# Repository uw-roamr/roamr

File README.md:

# ROAMR: Really Opensource Autonomous Mobile Robot

Mobile phones and mobile robots have many common requirements:

- performant sensors (cameras, IMUs, LiDAR, GPS) and sensor fusion
- networking capabilities (WiFi, Bluetooth Low Energy, LTE)
- energy efficiency

What if we turned the iPhone into a robot?

## Architecture

### iOS host app:

- exposes the core sensor data through iOS APIs
    - Camera
    - LiDAR (iPhone Pro 12+)
    - IMU
- runs WASM bytecode using statically compiled WAMR iwasm
- communicates with ESP32 over BLE to control motors

### WASM module:

- imports read sensor functions from iOS host
- multi-threaded application with autonomy logic
- compiled using WASI-SDK and threading
    - C++: https://github.com/WebAssembly/wasi-sdk

### ESP32:

- recieves commands over BLE and uses SimpleFOC to control motors

## Setup

```sh
pip install pre-commit
pre-commit
```

## Run App with Robot
- Open/build iOS app.
- Connect to bluetooth using the app
- Drive robot!

### Optional:
- Open HTML page in webpage folder.
- Run websocket on the websocket page of the app
- Connect to app websocket
- Drive robot!

## Development

See [WASM/README.md](WASM/README.md)

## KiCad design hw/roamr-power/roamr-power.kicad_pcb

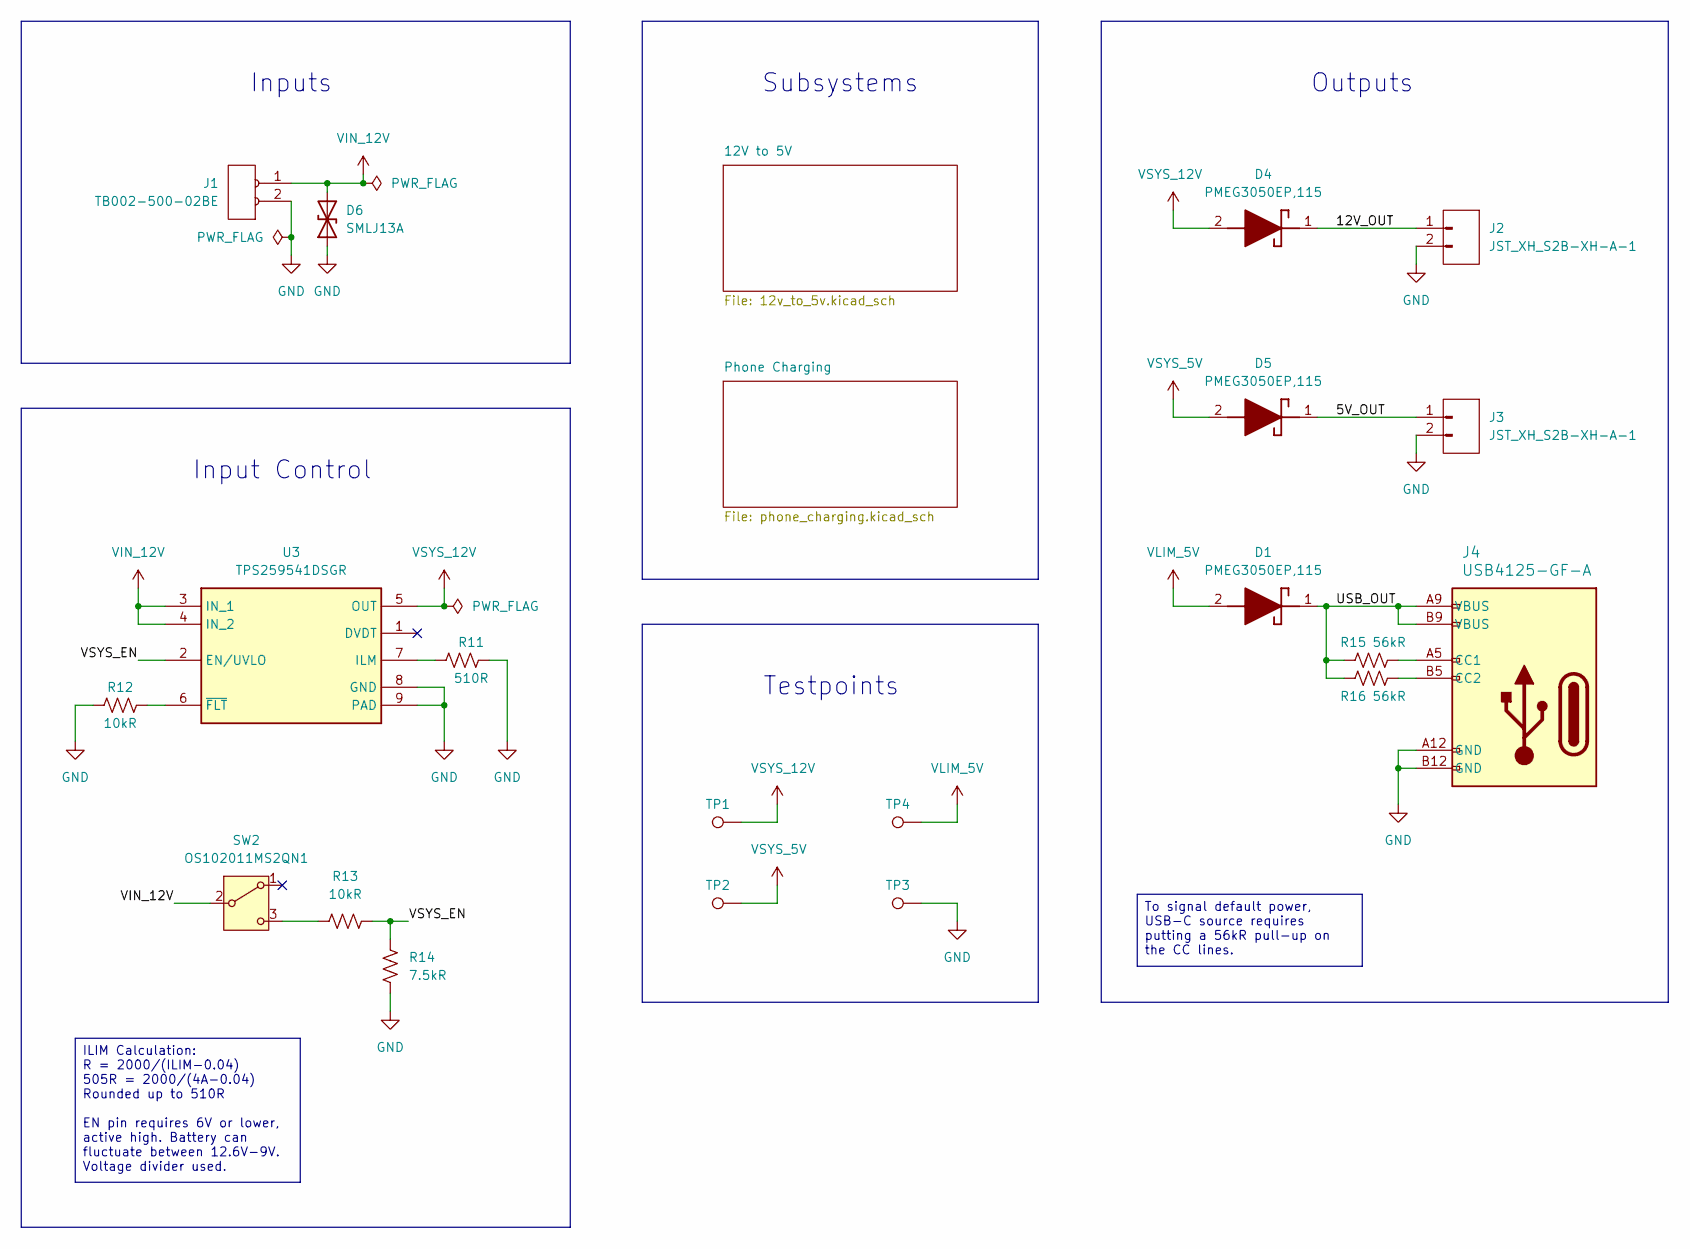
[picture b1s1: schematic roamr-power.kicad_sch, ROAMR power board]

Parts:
D1, D4, D5: PMEG3050EP,115; PMEG3050EP115; Mouser Part Number 771-PMEG3050EP115
D6: SMLJ13A; DIOM7959X262N; Manufacturer_Part_Number SMLJ13A
J1: TB002-500-02BE; TB00250002BE; Manufacturer_Part_Number TB002-500-02BE
J2, J3: JST_XH_S2B-XH-A-1; JST_XH_S2B-XH-A-1_1x02_P2.50mm_Horizontal; Manufacturer_Part_Number JST_XH_S2B-XH-A-1
J4: USB4125-GF-A; USB4125GFA; Manufacturer_Part_Number USB4125-GF-A
R11: 510R; R_0603_1608Metric
R12, R13: 10kR; R_0603_1608Metric
R14: 7.5kR; R_0603_1608Metric
R15, R16: 56kR; R_0603_1608Metric
SW2: OS102011MS2QN1; OS102011MA1QN1; Manufacturer_Part_Number OS102011MS2QN1
TP1, TP2, TP4: TestPoint; TestPoint_Pad_D1.5mm
TP3: TestPoint; TestPoint_Keystone_5005-5009_Compact; Manufacturer_Part_Number 5005-5009
U3: TPS259541DSGR; SON50P200X200X80-9N; Mouser Part Number 595-TPS259541DSGR

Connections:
/5V_OUT: D5.1 (K), J3.1
/12V_OUT: D4.1 (K), J2.1
/USB_OUT: D1.1 (K), J4.A9 (VBUS), J4.B4 (VBUS), J4.B9 (VBUS), R15.1, R16.1
/VSYS_EN: R13.2, R14.1, U3.2 (EN/UVLO)
GND: D6.1 (A1), J1.2, J2.2, J3.2, J4.A12 (GND), J4.B12 (GND), R11.2, R12.1, R14.2, TP3.1, U3.8 (GND), U3.9 (PAD); also elsewhere on the board
unnamed: J4.A5 (CC1), R15.2
unnamed: J4.B5 (CC2), R16.2
unnamed: R13.1, SW2.3 (C)
unnamed: R11.1, U3.7 (ILM)
unnamed: R12.2, U3.6 (~FLT)
VIN_12V: D6.2 (A2), J1.1, SW2.2 (B), U3.3 (IN_1), U3.4 (IN_2)
VLIM_5V: D1.2 (A), TP4.1; also elsewhere on the board
VSYS_5V: D5.2 (A), TP2.1; also elsewhere on the board
VSYS_12V: D4.2 (A), TP1.1, U3.5 (OUT); also elsewhere on the board

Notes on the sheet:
Input Control
Inputs
Subsystems
Outputs
Testpoints
ILIM Calculation: R = 2000/(ILIM-0.04) 505R = 2000/(4A-0.04) Rounded up to 510R EN pin requires 6V or lower, active high. Battery can fluctuate between 12.6V-9V. Voltage divider used.
To signal default power, USB-C source requires putting a 56kR pull-up on the CC lines.

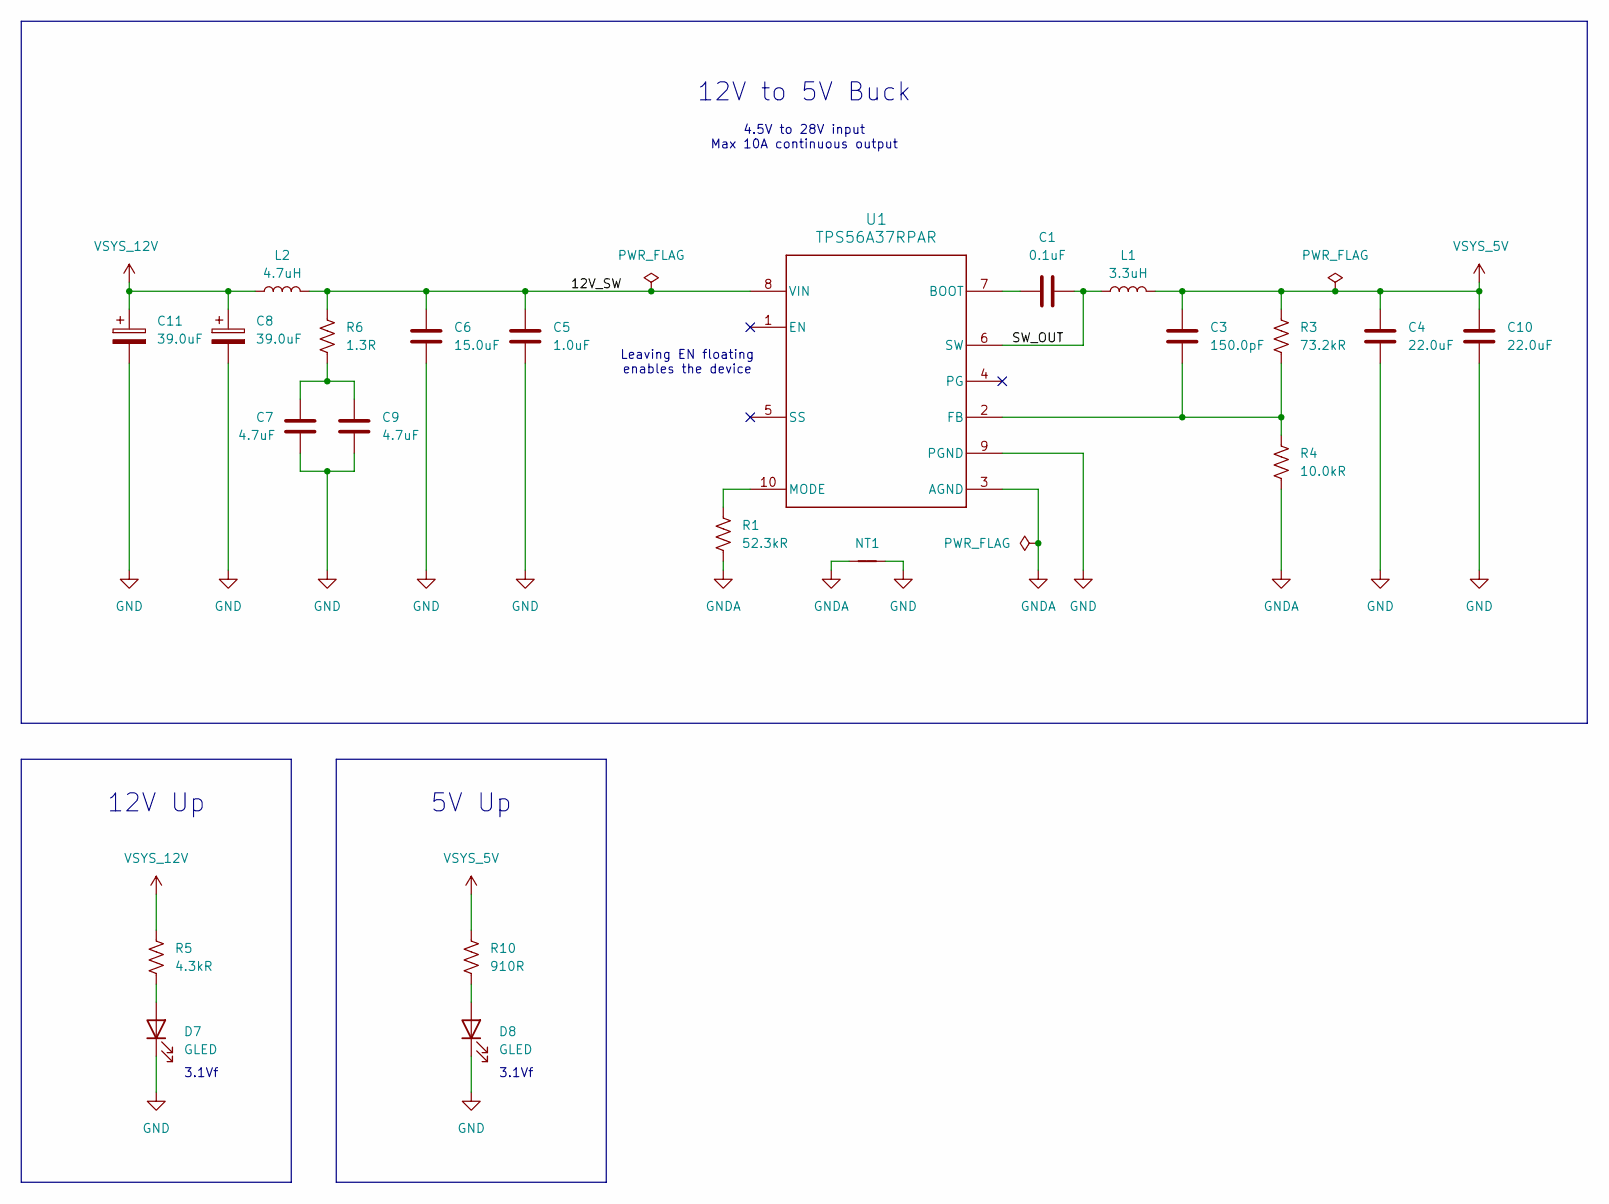
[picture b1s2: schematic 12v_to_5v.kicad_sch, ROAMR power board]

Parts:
C1: 0.1uF; C_0603_1608Metric
C3: 150.0pF; C_0603_1608Metric
C4, C10: 22.0uF; C_0603_1608Metric
C5: 1.0uF; C_0603_1608Metric
C6: 15.0uF; C_0805_2012Metric
C7, C9: 4.7uF; C_0603_1608Metric
C8, C11: 39.0uF; 16SVF270M
D7, D8: GLED; LEDC1608X70N; Manufacturer_Part_Number KT-0603G
L1: 3.3uH; IND_PCC-M0645M_PAN-L; Manufacturer_Part_Number ETQ-L4M3R3YFN
L2: 4.7uH; IND_VLS6045EX-4R7M_TDK; Manufacturer_Part_Number VLS6045EX
NT1: NetTie_2; NetTie-2_SMD_Pad0.5mm
R1: 52.3kR; R_0603_1608Metric
R3: 73.2kR; R_0603_1608Metric
R4: 10.0kR; R_0603_1608Metric
R5: 4.3kR; R_0603_1608Metric
R6: 1.3R; R_0603_1608Metric
R10: 910R; R_0603_1608Metric
U1: TPS56A37RPAR; RPA0010A-MFG; Manufacturer_Part_Number TPS56A37RPAR

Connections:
/12V to 5V/12V_SW: C5.1, C6.1, L2.2, R6.1, U1.8 (VIN)
/12V to 5V/SW_OUT: C1.2, L1.1, U1.6 (SW)
GND: C4.2, C5.2, C6.2, C7.2, C8.2, C9.2, C10.2, C11.2, D7.1 (K), D8.1 (K), NT1.2, U1.9 (PGND); also elsewhere on the board
GNDA: NT1.1, R1.1, R4.1, U1.3 (AGND)
unnamed: C7.1, C9.1, R6.2
unnamed: D7.2 (A), R5.2
unnamed: D8.2 (A), R10.2
unnamed: C1.1, U1.7 (BOOT)
unnamed: C3.2, R3.1, R4.2, U1.2 (FB)
unnamed: R1.2, U1.10 (MODE)
VSYS_5V: C3.1, C4.1, C10.1, L1.2, R3.2, R10.1; also elsewhere on the board
VSYS_12V: C8.1, C11.1, L2.1, R5.1; also elsewhere on the board

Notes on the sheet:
5V Up
3.1Vf
12V to 5V Buck
12V Up
3.1Vf
Leaving EN floating enables the device
4.5V to 28V input Max 10A continuous output

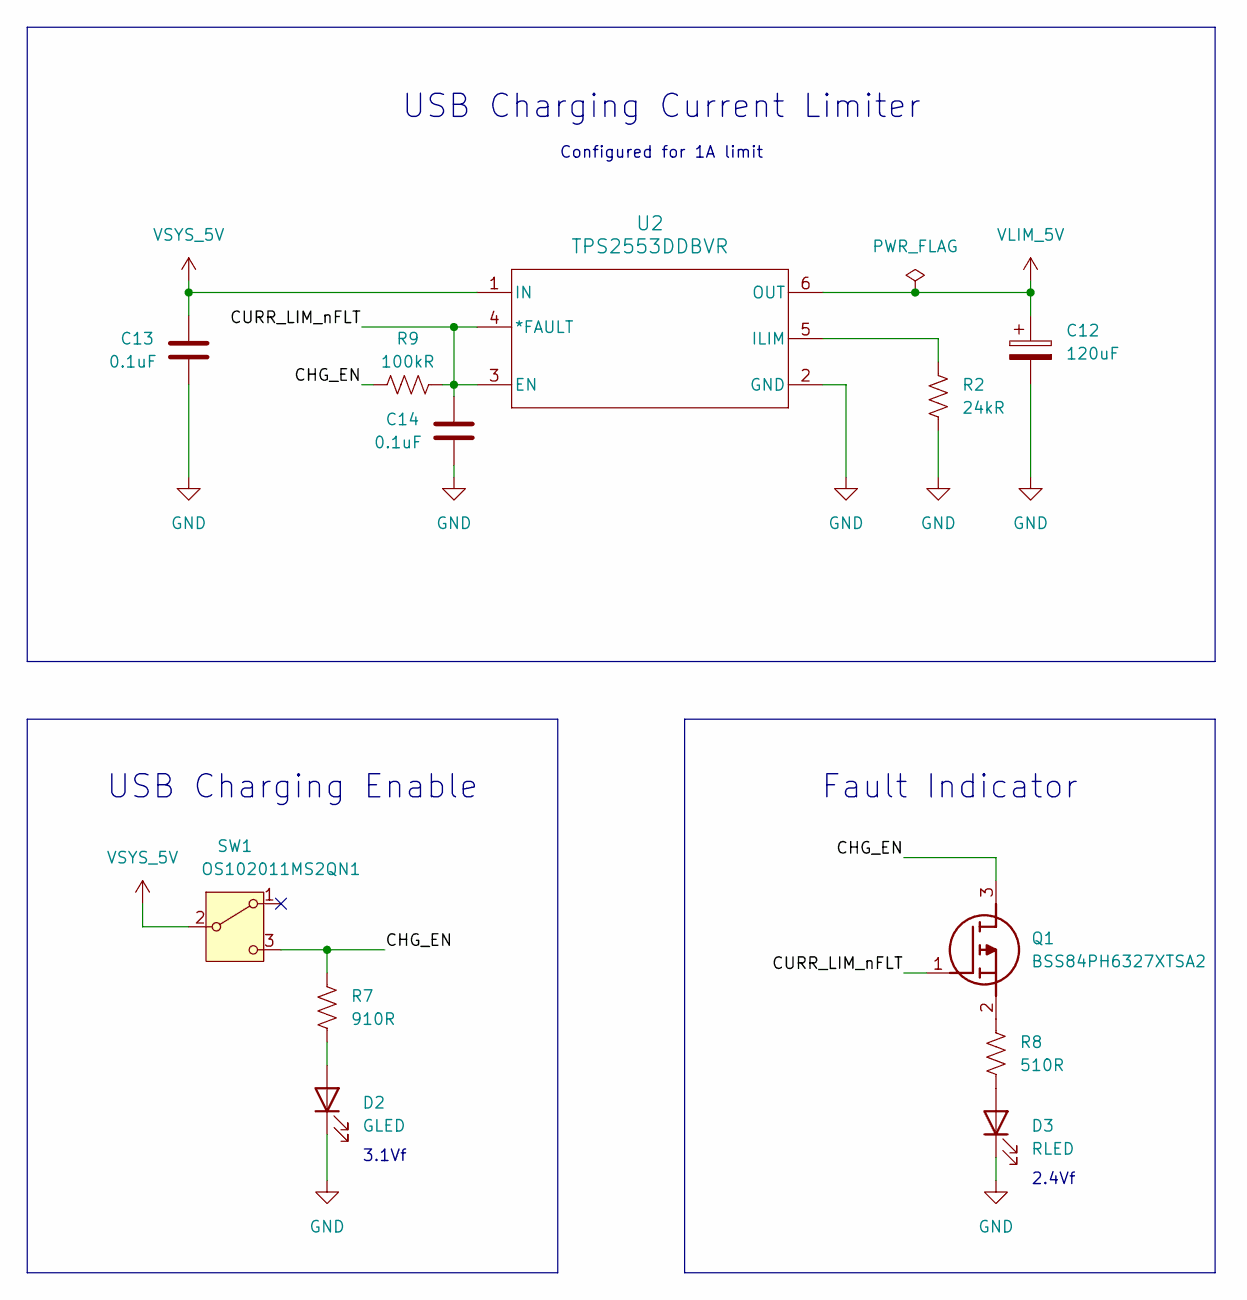
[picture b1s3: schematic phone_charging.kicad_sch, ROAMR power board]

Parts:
C12: 120uF; CAPAE660X610N
C13, C14: 0.1uF; C_0603_1608Metric
D2: GLED; LEDC1608X70N; Manufacturer_Part_Number KT-0603G
D3: RLED; LEDC1608X70N; Manufacturer_Part_Number KT-0603R
Q1: BSS84PH6327XTSA2; SOT95P240X110-3N; Mouser Part Number 726-BSS84PH6327XTSA2
R2: 24kR; R_0603_1608Metric
R7: 910R; R_0603_1608Metric
R8: 510R; R_0603_1608Metric
R9: 100kR; R_0603_1608Metric
SW1: OS102011MS2QN1; OS102011MA1QN1; Manufacturer_Part_Number OS102011MS2QN1
U2: TPS2553DDBVR; SOT95P280X145-6N; Manufacturer_Part_Number TPS2553DDBVR

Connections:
/Phone Charging/CHG_EN: Q1.3 (D), R7.1, R9.1, SW1.3 (C)
/Phone Charging/CURR_LIM_nFLT: C14.1, Q1.1 (G), R9.2, U2.3 (EN), U2.4 (*FAULT)
GND: C12.2, C13.2, C14.2, D2.1 (K), D3.1 (K), R2.2, U2.2 (GND); also elsewhere on the board
unnamed: D2.2 (A), R7.2
unnamed: D3.2 (A), R8.2
unnamed: Q1.2 (S), R8.1
unnamed: R2.1, U2.5 (ILIM)
VLIM_5V: C12.1, U2.6 (OUT); also elsewhere on the board
VSYS_5V: C13.1, SW1.2 (B), U2.1 (IN); also elsewhere on the board

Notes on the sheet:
USB Charging Enable
3.1Vf
USB Charging Current Limiter
2.4Vf
Fault Indicator
Configured for 1A limit

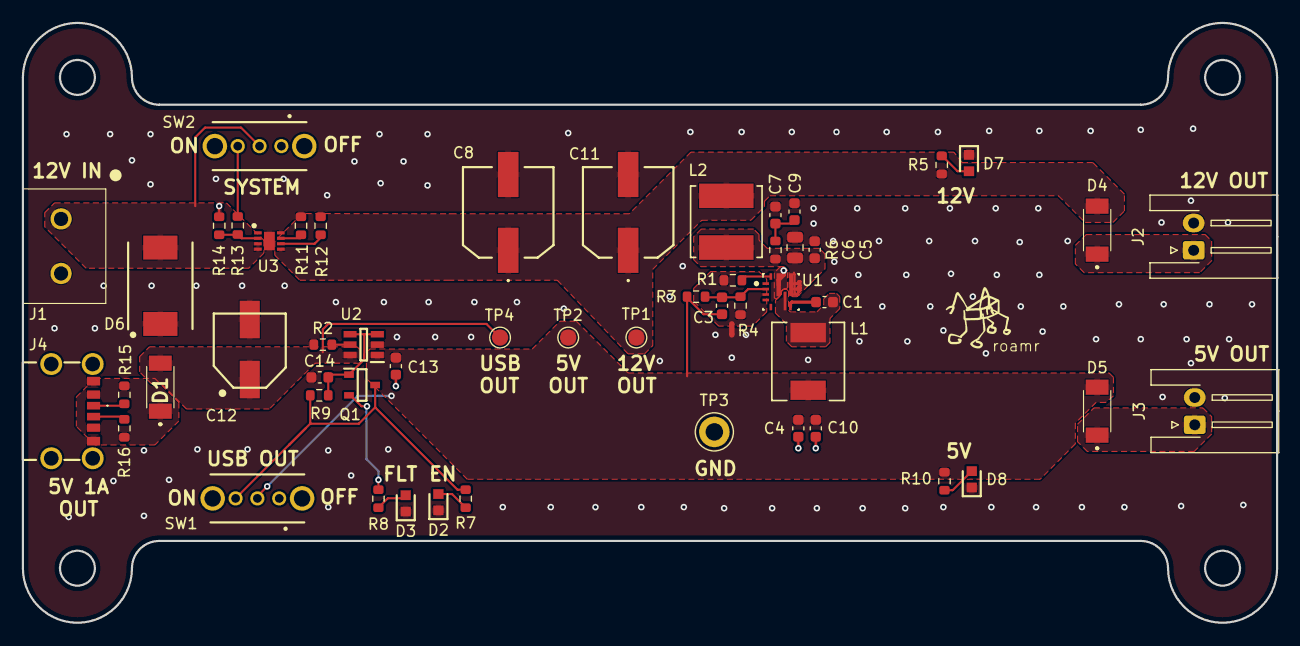
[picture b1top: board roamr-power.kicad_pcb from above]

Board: 2 copper layers, 115.0 x 55.0 mm, 54 parts (0 on the bottom side), 29 nets.

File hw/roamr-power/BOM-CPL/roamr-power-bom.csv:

"Reference","Qty","Value","Manufacturer_Part_Number","DNP","Exclude from BOM","Exclude from Board","Footprint","Datasheet"
"C1,C13,C14","3","0.1uF","","","","","Capacitor_SMD:C_0603_1608Metric","~"
"C3","1","150.0pF","","","","","Capacitor_SMD:C_0603_1608Metric","~"
"C4,C10","2","22.0uF","","","","","Capacitor_SMD:C_0603_1608Metric","~"
"C5","1","1.0uF","","","","","Capacitor_SMD:C_0603_1608Metric","~"
"C6","1","15.0uF","","","","","Capacitor_SMD:C_0805_2012Metric","~"
"C7,C9","2","4.7uF","","","","","Capacitor_SMD:C_0603_1608Metric","~"
"C8,C11","2","39.0uF","","","","","35SVPF39M:16SVF270M","~"
"C12","1","120uF","","","","","GYG1E121MCQ1GS:CAPAE660X610N","~"
"D1,D4,D5","3","PMEG3050EP,115","PMEG3050EP,115","","","","PMEG3050EP:PMEG3050EP115","https://assets.nexperia.com/documents/data-sheet/PMEG3050EP.pdf"
"D2,D7,D8","3","GLED","KT-0603G","","","","KT-0603:LEDC1608X70N","~"
"D3","1","RLED","KT-0603R","","","","KT-0603:LEDC1608X70N","~"
"D6","1","SMLJ13A","SMLJ13A","","","","SMLJ13CA-R:DIOM7959X262N","~"
"J1","1","TB002-500-02BE","TB002-500-02BE","","","","TB002-500-02BE:TB00250002BE","~"
"J2,J3","2","JST_XH_S2B-XH-A-1","JST_XH_S2B-XH-A-1","","","","Connector_JST:JST_XH_S2B-XH-A-1_1x02_P2.50mm_Horizontal","~"
"J4","1","USB4125-GF-A","USB4125-GF-A","","","","USB4125-GF-A:USB4125GFA","USB4125-GF-A"
"L1","1","3.3uH","ETQ-L4M3R3YFN","","","","ETQ-P4M3R3YFN:IND_PCC-M0645M_PAN-L","~"
"L2","1","4.7uH","VLS6045EX","","","","VLS6045EX_4R7M:IND_VLS6045EX-4R7M_TDK","~"
"NT1","1","NetTie_2","","","Excluded from BOM","","NetTie:NetTie-2_SMD_Pad0.5mm","~"
"Q1","1","BSS84PH6327XTSA2","BSS84PH6327XTSA2","","","","BSS84PH6327XTSA2:SOT95P240X110-3N","https://componentsearchengine.com/Datasheets/2/BSS84PH6327XTSA2.pdf"
"R1","1","52.3kR","","","","","Resistor_SMD:R_0603_1608Metric","~"
"R2","1","24kR","","","","","Resistor_SMD:R_0603_1608Metric","~"
"R3","1","73.2kR","","","","","Resistor_SMD:R_0603_1608Metric","~"
"R4","1","10.0kR","","","","","Resistor_SMD:R_0603_1608Metric","~"
"R5","1","4.3kR","","","","","Resistor_SMD:R_0603_1608Metric","~"
"R6","1","1.3R","","","","","Resistor_SMD:R_0603_1608Metric","~"
"R7,R10","2","910R","","","","","Resistor_SMD:R_0603_1608Metric","~"
"R8,R11","2","510R","","","","","Resistor_SMD:R_0603_1608Metric","~"
"R9","1","100kR","","","","","Resistor_SMD:R_0603_1608Metric","~"
"R12,R13","2","10kR","","","","","Resistor_SMD:R_0603_1608Metric","~"
"R14","1","7.5kR","","","","","Resistor_SMD:R_0603_1608Metric","~"
"R15,R16","2","56kR","","","","","Resistor_SMD:R_0603_1608Metric","~"
"SW1,SW2","2","OS102011MS2QN1","OS102011MS2QN1","","","","OS102011MS2QN1:OS102011MA1QN1","~"
"TP1,TP2,TP4","3","TestPoint","","","","","TestPoint:TestPoint_Pad_D1.5mm","~"
"TP3","1","TestPoint","5005-5009","","","","TestPoint:TestPoint_Keystone_5005-5009_Compact","~"
"U1","1","TPS56A37RPAR","TPS56A37RPAR","","","","TPS56A37RPAR:RPA0010A-MFG","https://www.ti.com/lit/gpn/tps56a37"
"U2","1","TPS2553DDBVR","TPS2553DDBVR","","","","TPS2553DDBVR:SOT95P280X145-6N","https://www.ti.com/lit/gpn/tps2553d"
"U3","1","TPS259541DSGR","TPS259541DSGR","","","","TPS259541DSGR:SON50P200X200X80-9N","http://www.ti.com/lit/gpn/tps2595"

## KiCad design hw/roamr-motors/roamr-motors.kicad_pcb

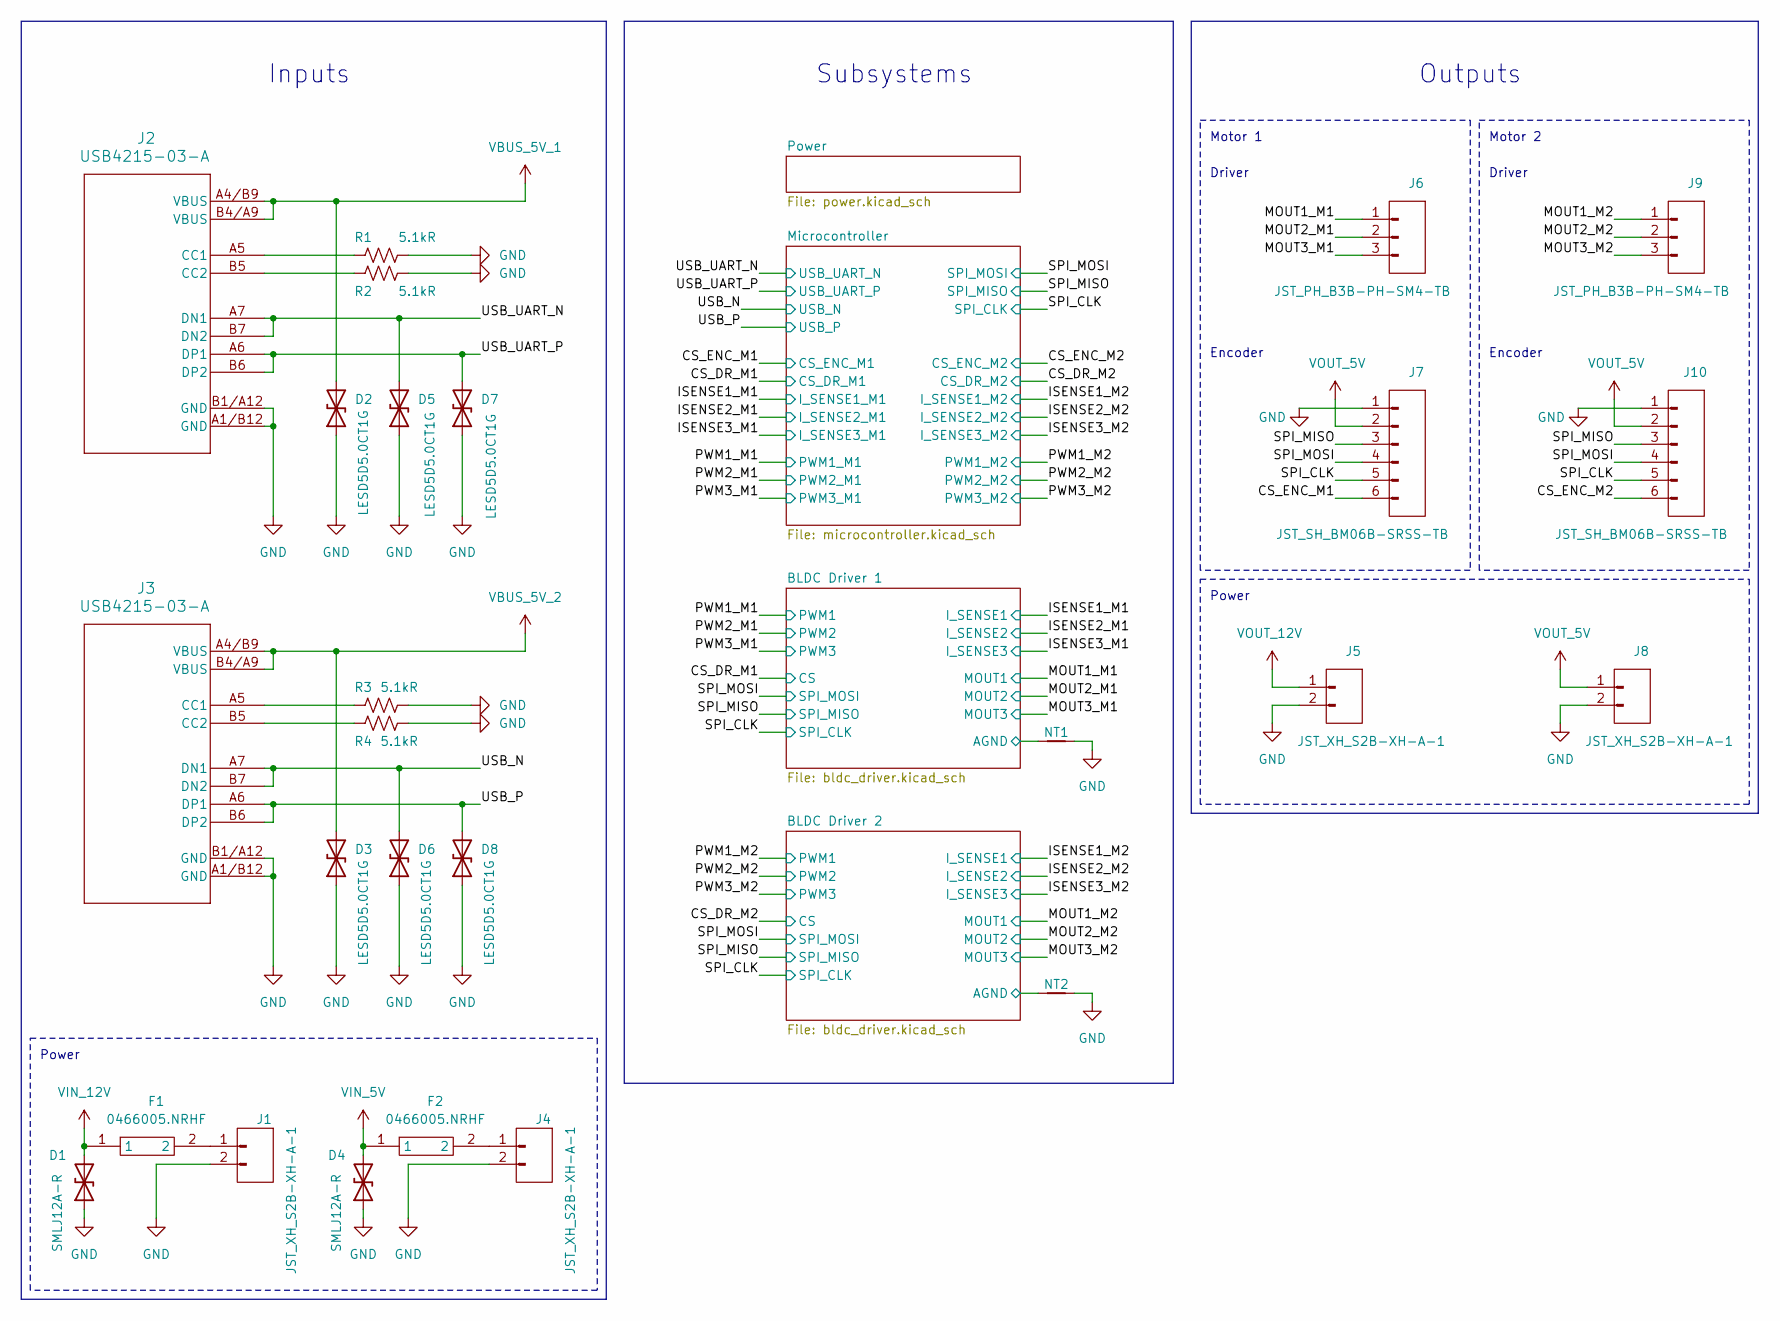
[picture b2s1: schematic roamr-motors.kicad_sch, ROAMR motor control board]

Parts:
D1, D4: SMLJ12A-R; DIOM7959X262N
D2, D3, D5, D6, D7, D8: LESD5D5.0CT1G; LESD5D50CT1G
F1, F2: 0466005.NRHF; F1206; LCSC Part C57525
J1, J4, J5, J8: JST_XH_S2B-XH-A-1; JST_XH_S2B-XH-A-1_1x02_P2.50mm_Horizontal
J2, J3: USB4215-03-A; CONN_8p94X6p5X3p16_12L_GCC
J6, J9: JST_PH_B3B-PH-SM4-TB; JST_PH_B3B-PH-SM4-TB_1x03-1MP_P2.00mm_Vertical
J7, J10: JST_SH_BM06B-SRSS-TB; JST_SH_BM06B-SRSS-TB_1x06-1MP_P1.00mm_Vertical
NT1, NT2: NetTie_2; NetTie-2_SMD_Pad0.5mm
R1, R2, R3, R4: 5.1kR; R_0603_1608Metric

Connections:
/BLDC Driver 1/AGND: NT1.1; also elsewhere on the board
/BLDC Driver 2/AGND: NT2.1; also elsewhere on the board
/CS_ENC_M1: J7.6; also elsewhere on the board
/CS_ENC_M2: J10.6; also elsewhere on the board
/MOUT1_M1: J6.1; also elsewhere on the board
/MOUT1_M2: J9.1; also elsewhere on the board
/MOUT2_M1: J6.2; also elsewhere on the board
/MOUT2_M2: J9.2; also elsewhere on the board
/MOUT3_M1: J6.3; also elsewhere on the board
/MOUT3_M2: J9.3; also elsewhere on the board
/SPI_CLK: J7.5, J10.5; also elsewhere on the board
/SPI_MISO: J7.3, J10.3; also elsewhere on the board
/SPI_MOSI: J7.4, J10.4; also elsewhere on the board
/USB_N: D6.2 (A2), J3.A7 (DN1), J3.B7 (DN2); also elsewhere on the board
/USB_P: D8.2 (A2), J3.A6 (DP1), J3.B6 (DP2); also elsewhere on the board
/USB_UART_N: D5.2 (A2), J2.A7 (DN1), J2.B7 (DN2); also elsewhere on the board
/USB_UART_P: D7.2 (A2), J2.A6 (DP1), J2.B6 (DP2); also elsewhere on the board
GND: D1.1 (A1), D2.1 (A1), D3.1 (A1), D4.1 (A1), D5.1 (A1), D6.1 (A1), D7.1 (A1), D8.1 (A1), J1.2, J2.A1/B12 (GND), J2.B1/A12 (GND), J3.A1/B12 (GND), J3.B1/A12 (GND), J4.2, J5.2, J7.1, J8.2, J10.1, NT1.2, NT2.2, R1.2, R2.2, R3.2, R4.2; also elsewhere on the board
unnamed: F1.2, J1.1
unnamed: J2.A5 (CC1), R1.1
unnamed: J2.B5 (CC2), R2.1
unnamed: J3.A5 (CC1), R3.1
unnamed: J3.B5 (CC2), R4.1
unnamed: F2.2, J4.1
VBUS_5V_1: D2.2 (A2), J2.A4/B9 (VBUS), J2.B4/A9 (VBUS); also elsewhere on the board
VBUS_5V_2: D3.2 (A2), J3.A4/B9 (VBUS), J3.B4/A9 (VBUS); also elsewhere on the board
VIN_5V: D4.2 (A2), F2.1; also elsewhere on the board
VIN_12V: D1.2 (A2), F1.1; also elsewhere on the board
VOUT_5V: J7.2, J8.1, J10.2; also elsewhere on the board
VOUT_12V: J5.1; also elsewhere on the board

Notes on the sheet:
Power
Outputs
Inputs
Encoder
Subsystems
Driver
Motor 2
Motor 1

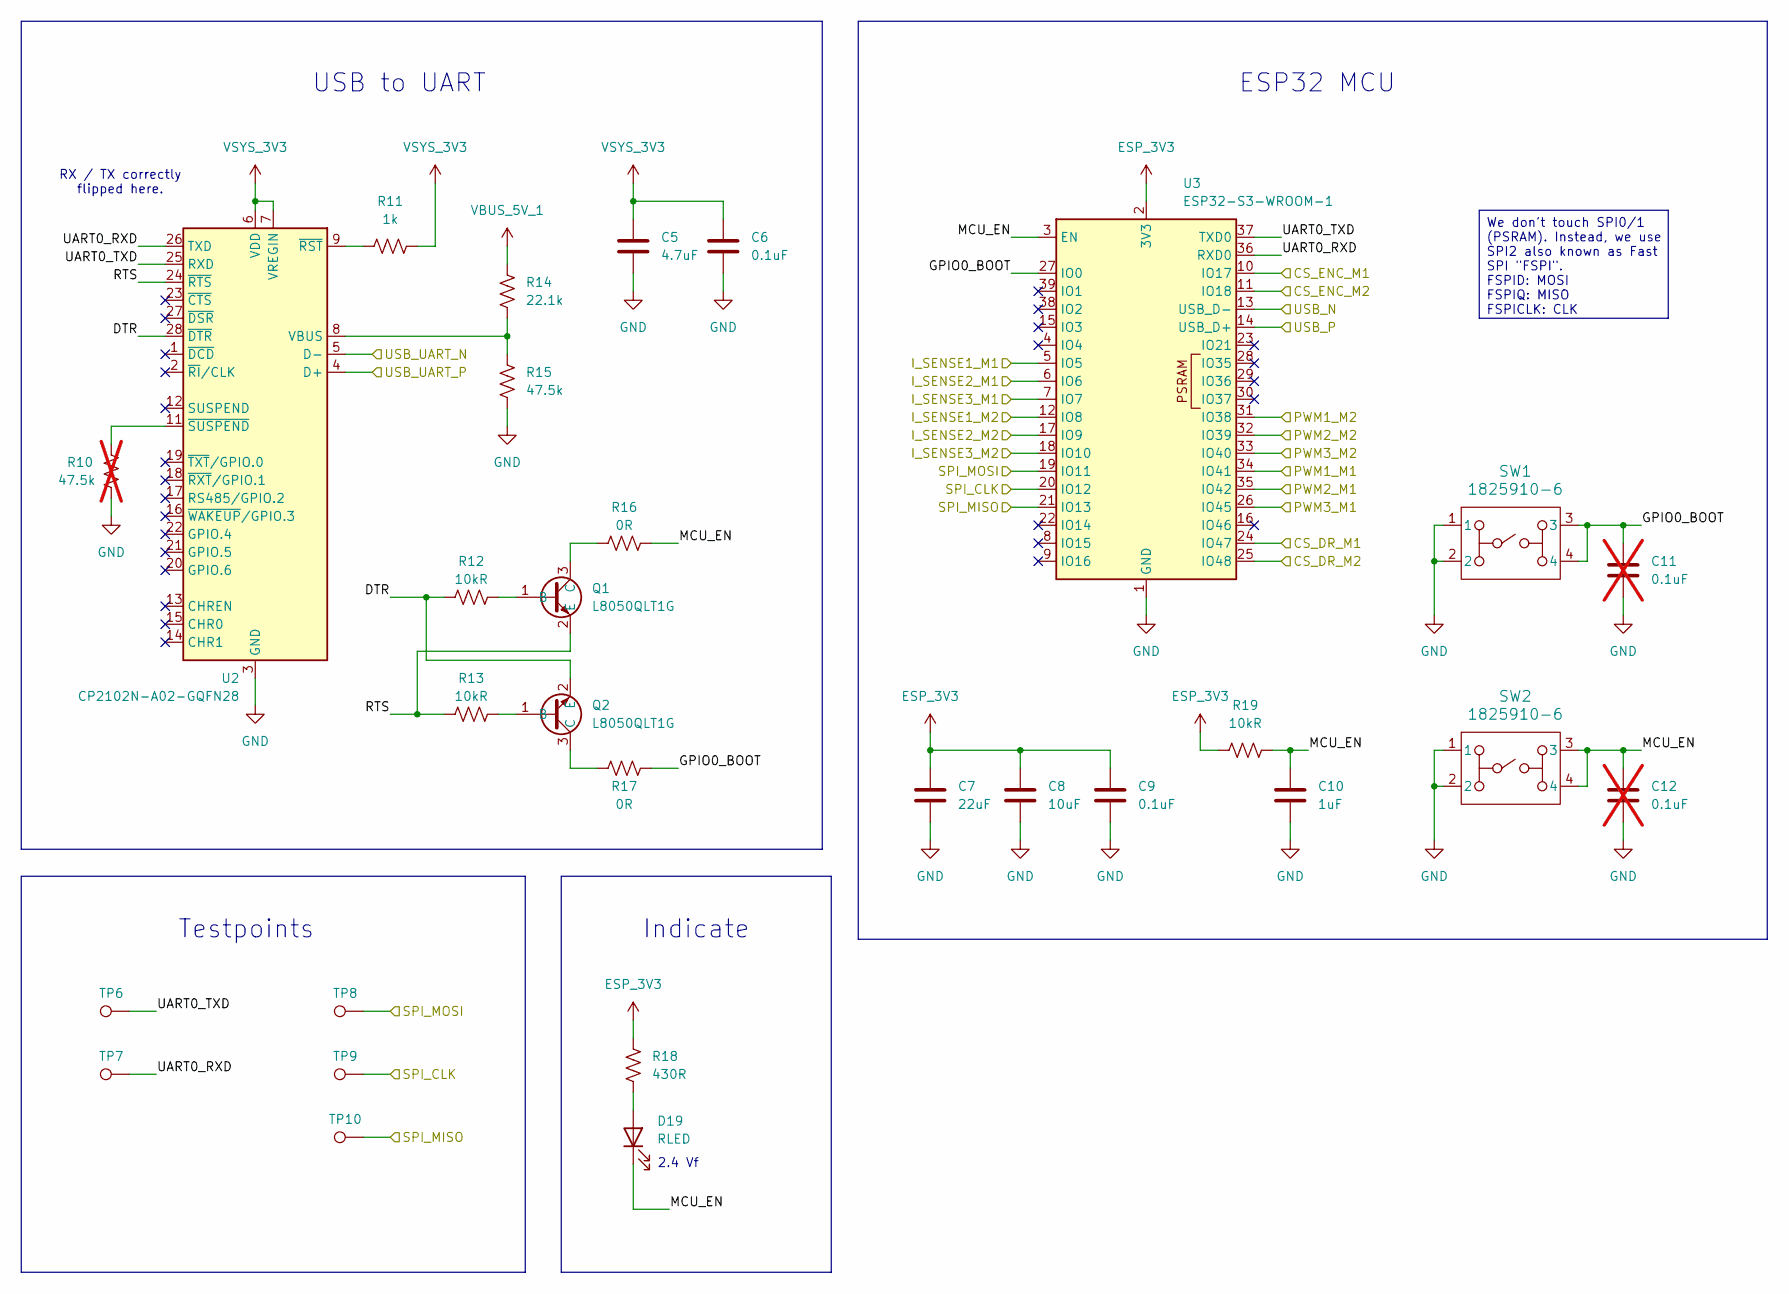
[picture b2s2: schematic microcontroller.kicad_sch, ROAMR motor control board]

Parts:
C5: 4.7uF; C_0603_1608Metric
C6, C9: 0.1uF; C_0603_1608Metric
C7: 22uF; C_0603_1608Metric
C8: 10uF; C_0603_1608Metric
C10: 1uF; C_0603_1608Metric
C11, C12: 0.1uF; C_0603_1608Metric; not fitted
D19: RLED; LEDC1608X70N
Q1, Q2: L8050QLT1G; Manufacturer_Part_Number L8050QLT1G
R10: 47.5k; R_0603_1608Metric; not fitted
R11: 1k; R_0603_1608Metric
R12, R13, R19: 10kR; R_0603_1608Metric
R14: 22.1k; R_0603_1608Metric
R15: 47.5k; R_0603_1608Metric
R16, R17: 0R; R_0603_1608Metric
R18: 430R; R_0603_1608Metric
SW1, SW2: 1825910-6; SW4_1825910-B_TEC
TP6, TP7, TP8, TP9, TP10: TestPoint; TestPoint_Pad_D1.5mm
U2: CP2102N-A02-GQFN28; QFN-28-1EP_5x5mm_P0.5mm_EP3.35x3.35mm
U3: ESP32-S3-WROOM-1

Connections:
/CS_DR_M1: U3.24 (IO47); also elsewhere on the board
/CS_DR_M2: U3.25 (IO48); also elsewhere on the board
/CS_ENC_M1: U3.10 (IO17); also elsewhere on the board
/CS_ENC_M2: U3.11 (IO18); also elsewhere on the board
/ISENSE1_M1: U3.5 (IO5); also elsewhere on the board
/ISENSE1_M2: U3.12 (IO8); also elsewhere on the board
/ISENSE2_M1: U3.6 (IO6); also elsewhere on the board
/ISENSE2_M2: U3.17 (IO9); also elsewhere on the board
/ISENSE3_M1: U3.7 (IO7); also elsewhere on the board
/ISENSE3_M2: U3.18 (IO10); also elsewhere on the board
/Microcontroller/DTR: Q2.2 (E), R12.1, U2.28 (~DTR)
/Microcontroller/GPIO0_BOOT: C11.1, R17.2, SW1.3, SW1.4, U3.27 (IO0)
/Microcontroller/MCU_EN: C10.1, C12.1, D19.1 (K), R16.2, R19.2, SW2.3, SW2.4, U3.3 (EN)
/Microcontroller/RTS: Q1.2 (E), R13.1, U2.24 (~RTS)
/Microcontroller/UART0_RXD: TP7.1, U2.26 (TXD), U3.36 (RXD0)
/Microcontroller/UART0_TXD: TP6.1, U2.25 (RXD), U3.37 (TXD0)
/PWM1_M1: U3.34 (IO41); also elsewhere on the board
/PWM1_M2: U3.31 (IO38); also elsewhere on the board
/PWM2_M1: U3.35 (IO42); also elsewhere on the board
/PWM2_M2: U3.32 (IO39); also elsewhere on the board
/PWM3_M1: U3.26 (IO45); also elsewhere on the board
/PWM3_M2: U3.33 (IO40); also elsewhere on the board
/SPI_CLK: TP9.1, U3.20 (IO12); also elsewhere on the board
/SPI_MISO: TP10.1, U3.21 (IO13); also elsewhere on the board
/SPI_MOSI: TP8.1, U3.19 (IO11); also elsewhere on the board
/USB_N: U3.13 (USB_D-); also elsewhere on the board
/USB_P: U3.14 (USB_D+); also elsewhere on the board
/USB_UART_N: U2.5 (D-); also elsewhere on the board
/USB_UART_P: U2.4 (D+); also elsewhere on the board
ESP_3V3: C7.1, C8.1, C9.1, R18.2, R19.1, U3.2 (3V3); also elsewhere on the board
GND: C5.2, C6.2, C7.2, C8.2, C9.2, C10.2, C11.2, C12.2, R10.1, R15.1, SW1.1, SW1.2, SW2.1, SW2.2, U2.3 (GND), U2.29 (GND), U3.1 (GND), U3.40 (GND), U3.41 (GND); also elsewhere on the board
unnamed: D19.2 (A), R18.1
unnamed: Q1.1 (B), R12.2
unnamed: Q1.3 (C), R16.1
unnamed: Q2.1 (B), R13.2
unnamed: Q2.3 (C), R17.1
unnamed: R14.1, R15.2, U2.8 (VBUS)
unnamed: R11.1, U2.9 (~RST)
unnamed: R10.2, U2.11 (~SUSPEND)
VBUS_5V_1: R14.2; also elsewhere on the board
VSYS_3V3: C5.1, C6.1, R11.2, U2.6 (VDD), U2.7 (VREGIN); also elsewhere on the board

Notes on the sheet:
2.4 Vf
Indicate
RX / TX correctly flipped here.
USB to UART
ESP32 MCU
Testpoints
We don't touch SPI0/1 (PSRAM). Instead, we use SPI2 also known as Fast SPI "FSPI". FSPID: MOSI FSPIQ: MISO FSPICLK: CLK
